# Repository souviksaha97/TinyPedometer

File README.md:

# TinyPedometer
ATTiny85 Based Pedometer using MPU6050 and SSD1306 OLED Screen

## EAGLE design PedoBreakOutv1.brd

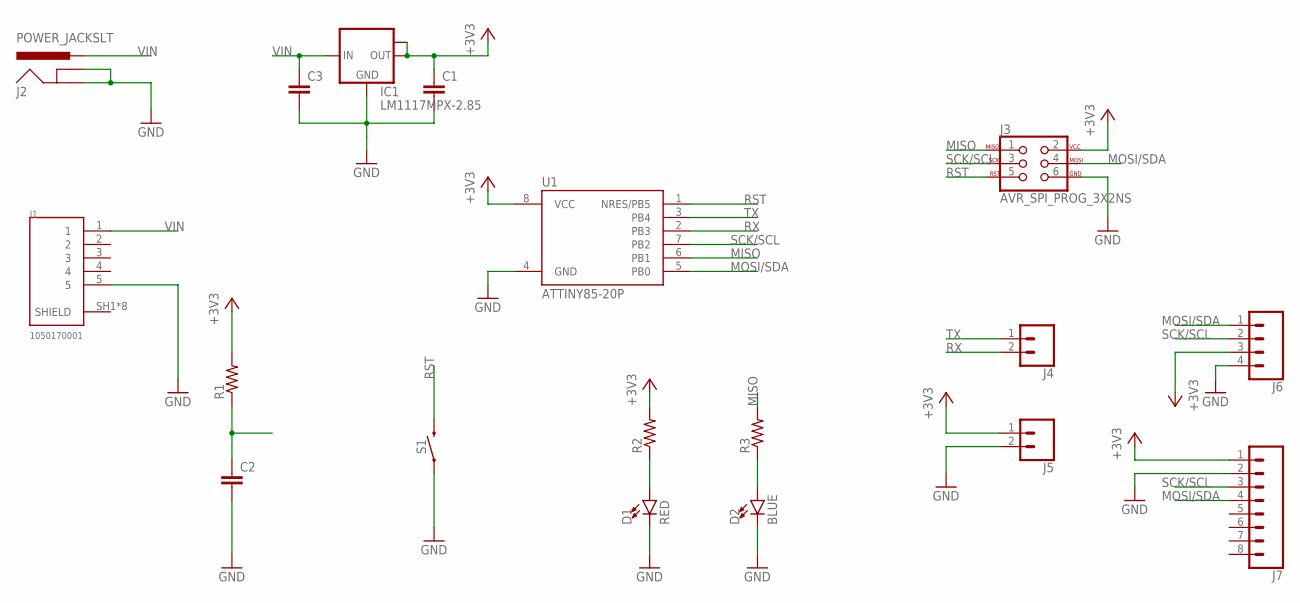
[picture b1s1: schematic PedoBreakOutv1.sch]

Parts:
C1, C2, C3: C-EUC0805; C0805
D1: RED; LED-0603
D2: BLUE; LED-0603
IC1: LM1117MPX-2.85; SOT223
J1: 1050170001; MOLEX_1050170001
J2: POWER_JACKSLT; POWER_JACK_SLOT
J3: AVR_SPI_PROG_3X2NS; 2X3-NS
J4, J5: CONN_02; 1X02
J6: CONN_041X04_NO_SILK; 1X04_NO_SILK
J7: CONN_08NO_SILK_FEMALE_PTH; 1X08_NO_SILK
R1, R2, R3: R-US_M0805; M0805
S1: MOMENTARY-SWITCH-SPST-PTH-6.0MM; TACTILE_SWITCH_PTH_6.0MM
U1: ATTINY85-20P; PDIP08_300MIL

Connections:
+3V3: C1.1, IC1.2 (OUT), IC1.TAB (OUT1), J3.2, J5.1, J6.3, J7.1, R1.2, R2.2, U1.8 (VCC)
GND: C1.2, C2.2, C3.2, D1.C, D2.C, IC1.1 (GND), J1.5, J2.GND@1 (GNDBREAK), J2.GND@2 (GND), J3.6, J5.2, J6.4, J7.2, S1.1, U1.4 (GND)
MISO: J3.1, R3.2, U1.6 (PB1)
MOSI/SDA: J3.4, J6.1, J7.4, U1.5 (PB0)
unnamed: D1.A, R2.1
unnamed: C2.1, R1.1
unnamed: D2.A, R3.1
RST: J3.5, S1.3 (2), U1.1 (NRES/PB5)
RX: J4.2, U1.2 (PB3)
SCK/SCL: J3.3, J6.2, J7.3, U1.7 (PB2)
TX: J4.1, U1.3 (PB4)
VIN: C3.1, IC1.3 (IN), J1.1, J2.PWR

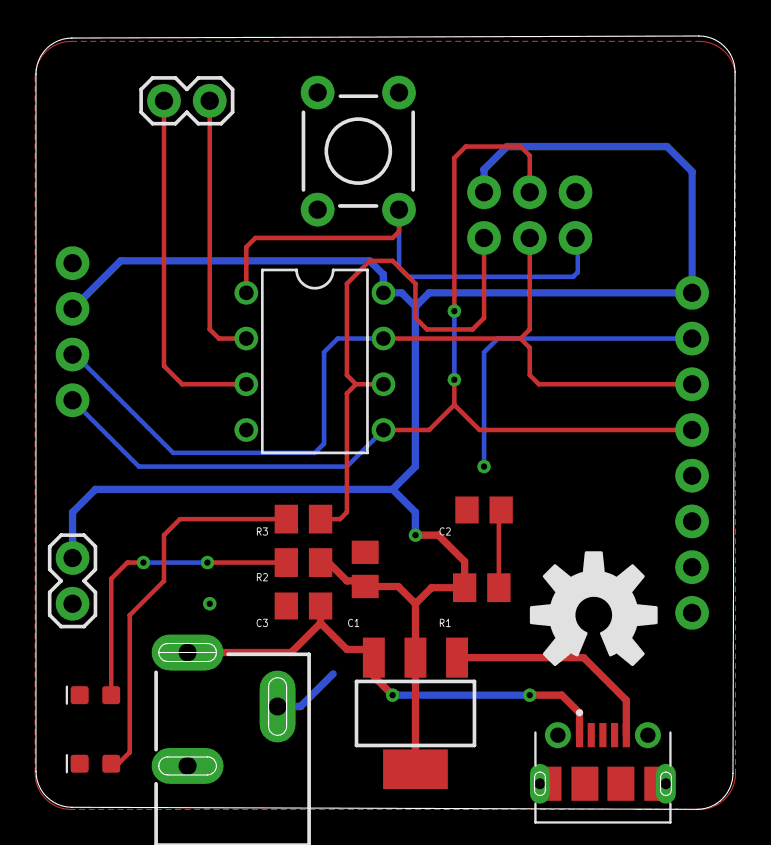
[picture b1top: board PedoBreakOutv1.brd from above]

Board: 2 copper layers, 38.8 x 43.0 mm, 19 parts (0 on the bottom side), 12 nets.

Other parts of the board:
U$1: OSHW-LOGO-L

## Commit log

2020-03-07 Reduced size of board, removed ground plane issues
2020-03-10 Added silkscreen logo, optimized GND plane
2020-03-14 Capacitor positioning, GND place modifications, aesthetics
2020-03-14 Removed U1 label

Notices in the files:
parts and their libraries:
SparkFun-Connectors: Licensing: Creative Commons ShareAlike 4.0 International - https://creativecommons.org/licenses/by-sa/4.0
